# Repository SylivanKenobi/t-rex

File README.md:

# T-Rex

A 5x12 Ortholinear QMK and ZMK compatible Keyboard. The keyboard is designed to be easily ordered by anyone from a PCB manufacturer and assembled by yourself. It is compatible with Pro Micro controllers and their derivatives. Additionally, it supports WS2812 LED strips as an extra feature. The keyboard comes with an assortment of 3D printable cases and can be assembled with easily available parts. 

QMK Firmware is currently only on this fork of [qmk](https://github.com/SylivanKenobi/qmk_firmware/tree/master/keyboards/t_rex). 

The [ZMK](https://github.com/devilzmods/trex_shield_module) implementation supports Bluetooth and ZMK Studio with [compatible controllers](https://zmk.dev/docs/hardware#pro_micro). 

Example parts:
* [QMK Controller](https://splitkb.com/products/pro-micro-atmega32u4-5v-16mhz)
* [ZMK Controller (Wireless)](https://de.aliexpress.com/item/1005007266112508.html)
* [Diodes](https://splitkb.com/products/tht-diodes)
* [Reset button](https://mechboards.co.uk/products/reset-switches?variant=40823623090381)
* 60 Switches
* 60 Keycaps
* 6x [M2x8 Standoffs](https://splitkb.com/products/brass-m2-spacers?variant=42396969173251)
* 3D printed case([stl file](cases/minimal-case.stl))
* 6x M2x10 screws, 6x M2x5 screws

## Assembly

### PCB

1. Solder diodes on top of board, orientation is marked by silkscreen
1. Clip diode leftovers
1. Solder controller headers and reset button
1. Solder switches
1. Solder controller
1. [Flash QMK](https://github.com/SylivanKenobi/qmk_firmware/tree/master/keyboards/t_rex)
1. [Or ZMK](firmware/t_rex_zmk_studio.uf2) - Download the .uf2 file, put the board into its bootloader by double tapping reset and copy the firmware file onto the controller.
1. For wireless, solder a battery (3,7V LiIon) or battery connector and power switch to the battery pins on the nice!nano.

> If you socket your controller, mount the controller before the switches and test the PCB.

### Cases

#### Minimal Case

1. Print [case](cases/minimal-case.stl) with 3d printer
1. Mount standoffs with M2x5 from the top
1. Mount case with M2x10 to standoffs

#### Closed Case

1. Print the case, depending on printer size you can either use the regular or the split version of the case.([case files](cases/closed-falt-case)) 
1. Insert M2x4x3.5 Heat set inserts([exapmle](https://www.bastelgarage.ch/gewindeeinsatze-messing-insert-set-360-stuck))
1. Mount pcb to case with M2x5 screws

#### Slab Case

1. Print the case, the .3mf file includes bodies for the lettering and Logo that can be colored for multicolor printing, removed for embossed text or ignored to fill the text in. Make sure the lid body sits flush on the build plate or print it separately. Only the main  Tray area of the case needs support, the battery cover can be printed in place as built-in support and popped out.[case file](cases/slabcase.3mf)
1. After printing remove the support and carefully break free the battery cover
1. Fill the case with your Medium of choice. Sand with a grain size of <2mm is recommended, other options include cement and plaster. The internal volume of the case is rougly .7 liter. Glue the lid on top and make sure it's tight in case your medium could spill out.
1. Mount 8mm standoffs to PCB with M2x5/6 from the top
1. Mount case with M2x5/6 to standoffs, if applicable route the battery connector wire into the battery tray.

## Plate

I would recommend using PCB-Mounted switches for this board. There is a 3d printable plate for the t-rex in this repo([file](cases/plate.stl)). The plate works but because it's 3d printed it's not that great.

## Customizing Firmware

(ZMK Studio)[https://zmk.studio/] allows on the fly remapping of your keyboards keymap, similar to via/vial. For more in-depth configuration you can follow the (ZMK Customization Guide)[https://zmk.dev/docs/customization] to create your own config repo and add the (T-Rex Shield Module)[https://github.com/devilzmods/trex_shield_module]

## Roadmap

1. Merge firmware to QMK

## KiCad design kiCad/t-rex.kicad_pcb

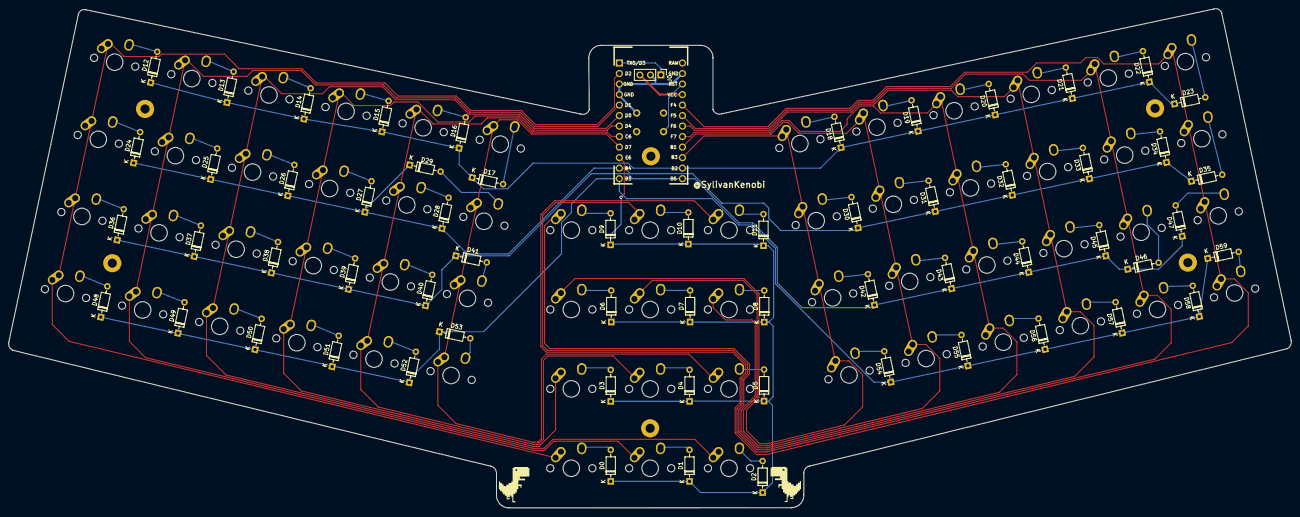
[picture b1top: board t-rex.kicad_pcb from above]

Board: 2 copper layers, 309.9 x 120.6 mm, 123 parts (1 on the bottom side), 81 nets.

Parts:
D0, D1, D2, D3, D4, D5, D6, D7, D8, D9, D10, D11, D12, D13, D14, D15, D16, D17, D18, D19, D20, D21, D22, D23, D24, D25, D26, D27, D28, D29, D30, D31, D32, D33, D34, D35, D36, D37, D38, D39, D40, D41, D42, D43, D44, D45, D46, D47, D48, D49, D50, D51, D52, D53, D54, D55, D56, D57, D58, D59: 1N4148; D_DO-35_SOD27_P7.62mm_Horizontal
J0: Conn_01x03; PinHeader_1x03_P2.54mm_Vertical
SW0, SW1, SW2, SW3, SW4, SW5, SW6, SW7, SW8, SW9, SW10, SW11, SW12, SW13, SW14, SW15, SW16, SW17, SW18, SW19, SW20, SW21, SW22, SW23, SW24, SW25, SW26, SW27, SW28, SW29, SW30, SW31, SW32, SW33, SW34, SW35, SW36, SW37, SW38, SW39, SW40, SW41, SW42, SW43, SW44, SW45, SW46, SW47, SW48, SW49, SW50, SW51, SW52, SW53, SW54, SW55, SW56, SW57, SW58, SW59: MX; MX-1U-NoLED
SW61: MX; PushButton_6x6mm_TH_Pretty
U0: Sparkfun_Pro_Micro; ArduinoProMicro

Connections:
+5V: J0.3, U0.21 (VCC)
/COL0: SW0.1, SW12.1, SW24.1, SW36.1, SW48.1, U0.2 (D0/RX)
/COL1: SW1.1, SW13.1, SW25.1, SW37.1, SW49.1, U0.5 (D2)
/COL2: SW2.1, SW14.1, SW26.1, SW38.1, SW50.1, U0.6 (~D3)
/COL3: SW3.1, SW15.1, SW27.1, SW39.1, SW51.1, U0.7 (D4/A6)
/COL4: SW4.1, SW16.1, SW28.1, SW40.1, SW52.1, U0.8 (~D5)
/COL5: SW5.1, SW17.1, SW29.1, SW41.1, SW53.1, U0.9 (~D6/A7)
/COL6: SW6.1, SW18.1, SW30.1, SW42.1, SW54.1, U0.15 (D14)
/COL7: SW7.1, SW19.1, SW31.1, SW43.1, SW55.1, U0.16 (D15)
/COL8: SW8.1, SW20.1, SW32.1, SW44.1, SW56.1, U0.17 (D18/A0)
/COL9: SW9.1, SW21.1, SW33.1, SW45.1, SW57.1, U0.18 (D19/A1)
/COL10: SW10.1, SW22.1, SW34.1, SW46.1, SW58.1, U0.19 (D20/A2)
/COL11: SW11.1, SW23.1, SW35.1, SW47.1, SW59.1, U0.20 (D21/A3)
/PIN15: J0.1, U0.1 (D1/TX)
/ROW0: D0.1 (K), D1.1 (K), D2.1 (K), D3.1 (K), D4.1 (K), D5.1 (K), D6.1 (K), D7.1 (K), D8.1 (K), D9.1 (K), D10.1 (K), D11.1 (K), U0.10 (D7)
/ROW1: D12.1 (K), D13.1 (K), D14.1 (K), D15.1 (K), D16.1 (K), D17.1 (K), D18.1 (K), D19.1 (K), D20.1 (K), D21.1 (K), D22.1 (K), D23.1 (K), U0.14 (D16)
/ROW2: D24.1 (K), D25.1 (K), D26.1 (K), D27.1 (K), D28.1 (K), D29.1 (K), D30.1 (K), D31.1 (K), D32.1 (K), D33.1 (K), D34.1 (K), D35.1 (K), U0.11 (D8/A8)
/ROW3: D36.1 (K), D37.1 (K), D38.1 (K), D39.1 (K), D40.1 (K), D41.1 (K), D42.1 (K), D43.1 (K), D44.1 (K), D45.1 (K), D46.1 (K), D47.1 (K), U0.13 (~D10/A10)
/ROW4: D48.1 (K), D49.1 (K), D50.1 (K), D51.1 (K), D52.1 (K), D53.1 (K), D54.1 (K), D55.1 (K), D56.1 (K), D57.1 (K), D58.1 (K), D59.1 (K), U0.12 (~D9/A9)
GND: J0.2, SW61.2, U0.3 (GND), U0.4 (GND), U0.23 (GND)
unnamed: D0.2 (A), SW0.2
unnamed: D1.2 (A), SW1.2
unnamed: D2.2 (A), SW2.2
unnamed: D3.2 (A), SW3.2
unnamed: D4.2 (A), SW4.2
unnamed: D5.2 (A), SW5.2
unnamed: D6.2 (A), SW6.2
unnamed: D7.2 (A), SW7.2
unnamed: D8.2 (A), SW8.2
unnamed: D9.2 (A), SW9.2
unnamed: D10.2 (A), SW10.2
unnamed: D11.2 (A), SW11.2
unnamed: D12.2 (A), SW12.2
unnamed: D13.2 (A), SW13.2
unnamed: D14.2 (A), SW14.2
unnamed: D15.2 (A), SW15.2
unnamed: D16.2 (A), SW16.2
unnamed: D17.2 (A), SW17.2
unnamed: D18.2 (A), SW18.2
unnamed: D19.2 (A), SW19.2
unnamed: D20.2 (A), SW20.2
unnamed: D21.2 (A), SW21.2
unnamed: D22.2 (A), SW22.2
unnamed: D23.2 (A), SW23.2
unnamed: D24.2 (A), SW24.2
unnamed: D25.2 (A), SW25.2
unnamed: D26.2 (A), SW26.2
unnamed: D27.2 (A), SW27.2
unnamed: D28.2 (A), SW28.2
unnamed: D29.2 (A), SW29.2
unnamed: D30.2 (A), SW30.2
unnamed: D31.2 (A), SW31.2
unnamed: D32.2 (A), SW32.2
unnamed: D33.2 (A), SW33.2
unnamed: D34.2 (A), SW34.2
unnamed: D35.2 (A), SW35.2
unnamed: D36.2 (A), SW36.2
unnamed: D37.2 (A), SW37.2
unnamed: D38.2 (A), SW38.2
unnamed: D39.2 (A), SW39.2
unnamed: D40.2 (A), SW40.2
unnamed: D41.2 (A), SW41.2
unnamed: D42.2 (A), SW42.2
unnamed: D43.2 (A), SW43.2
unnamed: D44.2 (A), SW44.2
unnamed: D45.2 (A), SW45.2
unnamed: D46.2 (A), SW46.2
unnamed: D47.2 (A), SW47.2
unnamed: D48.2 (A), SW48.2
unnamed: D49.2 (A), SW49.2
unnamed: D50.2 (A), SW50.2
unnamed: D51.2 (A), SW51.2
unnamed: D52.2 (A), SW52.2
unnamed: D53.2 (A), SW53.2
unnamed: D54.2 (A), SW54.2
unnamed: D55.2 (A), SW55.2
unnamed: D56.2 (A), SW56.2
unnamed: D57.2 (A), SW57.2
unnamed: D58.2 (A), SW58.2
unnamed: D59.2 (A), SW59.2
unnamed: SW61.1, U0.22 (RST)

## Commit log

2022-11-15 add kiCad files
2022-11-15 add readme
2022-11-15 add library submodules
2022-12-19 draw pcb, add more footprints
2023-01-17 add gerbers, fix labels
2023-01-17 update gerbers
2023-01-17 add ergogen yaml
2023-01-25 remove unused modules
2023-02-24 review changes
2023-03-05 release 1
2023-03-09 align silkscreen
2023-03-09 new layout with numbpad
2023-03-20 add traces
2023-03-20 finish routing, improve edge cuts, generate gerbers
2023-03-27 add basic case
2023-03-27 add images
2023-03-27 more docs
2023-04-09 add instructions and roadmap
2023-04-09 update to kicad 7, cleanup repo
2023-05-01 add closed case
2023-05-01 add plate
2023-05-01 update docs
2023-05-06 add stl for closed case
2023-06-14 fix missing mount holes in pcb
2024-02-03 update to newer kicad version
2025-11-09 Add a nice case and documentation for ZMK firmware support
2025-11-09 Add readymade .uf2 file for convenience
2025-11-23 replace regular case with improved version
